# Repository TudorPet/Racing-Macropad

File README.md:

# Racing-Macropad
The Racing Macropad is a compact, programmable input device based on the RP2040 microcontroller, designed for sim racing, gaming, and productivity use cases. It allows full key remapping, encoder customization, and RGB control. The rotary encoder can be used for functions such as brake bias, traction control, menu navigation, or volume control. The device uses Cherry MX–style mechanical switches and connects via USB. Its simple and modular design makes it ideal as a sim racing button box.

---
### Features:
* Compact 3×2 Key Matrix - 6 programmable inputs
* Rotary Encoder - programmable rotary encoder with push button
* 2x RGB LEDs - 2 LEDs for visual feedback
* 3D Printed Case

---
### CAD:
Designed using fusion. Everything fits together using 4x m3 screws and bolts:<br>

---
### Schematic and PCB:
Designed with kicad. I ran DRC and got 0 errors, only a few dismissible warnings. <br>
 <br>

---
### Firmware:
I wrote the firmware using QMK, which was definitely a change compared to what im used to. This was the part of the project that I was looking forward to the least (which may seem weird, as I do enjoy coding), and it turned out to be the most confusing one, too. With that being said, I am looking forward to learning more about QMK and improving.

---

### BOM:
* 1x Seeed XIAO RP2040 at €3.5 - €8.5 (~$4 - $9)
* 6x MX-Style switches at €0.50 - €0.60 (~$0.55 - $0.65) per switch, so €3 - €4 ($3.3 - $4.0) for 6 - if bought in bulk!
* 6x Keycaps at €0.2 (~$0.25) per key, so around €1.2 ($1.45) for 6 - if bought in bulk!
* 1x EC11 Rotary encoder at €4 - €5 (~$4.5 - $5.5)
* 4x M3x16mm screws and 4x M3x5mx4mm heatset inserts at €1 - €3 ($1.1 - $3)
* 1x PCB €5 - €12 ($6 - $13)
* 1x 3D Printed case €5 - €15 ($6 - $17)<br>
These prices are a sheer estimation and, by no means, 100% accurate. Many of these components can be found priced very differently, depending on location and source. The estimated total ranges between €20 and €50 (huge difference, I know!), however I believe it would cost around €30. A big part of the total is the 3d printed case, so the cost is greatly reduced if you own a 3D printer. 
---
### Notes:
This was my first time doing a project like this (and working with programs such as kicad and fusion - which i really enjoyed!). As someone familiar with algorithmics (that also occasionaly helps with repairing/building electronics), I found the design process really fun, however also a bit demanding for a person with so little experience. It took a little bit longer to finish the first version than i would have wanted, however im happy with the way it turned out. I want to keep working on it, implementing features such as syncing the leds to different titles and designing a stand compatible with different racing rigs.

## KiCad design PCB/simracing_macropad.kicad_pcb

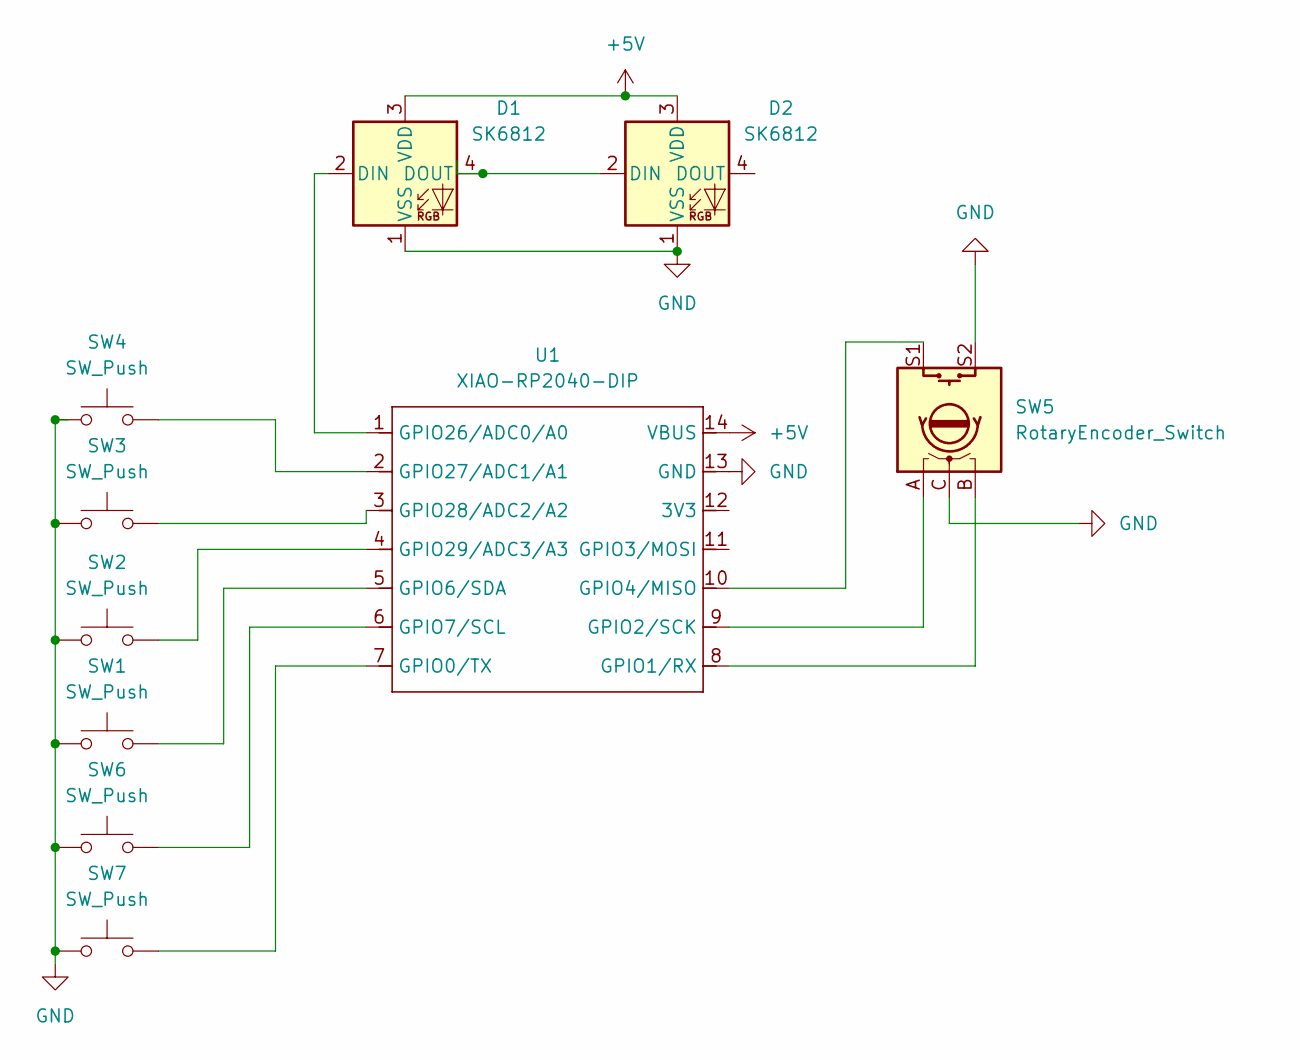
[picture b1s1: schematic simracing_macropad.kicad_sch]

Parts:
D1, D2: SK6812; LED_SK6812_PLCC4_5.0x5.0mm_P3.2mm
SW1, SW2, SW3, SW4, SW6, SW7: SW_Push; SW_Cherry_MX_1.00u_PCB
SW5: RotaryEncoder_Switch; RotaryEncoder_Alps_EC11E-Switch_Vertical_H20mm
U1: XIAO-RP2040-DIP

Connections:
+5V: D1.3 (VDD), D2.3 (VDD), U1.14 (VBUS)
GND: D1.1 (VSS), D2.1 (VSS), SW1.1, SW2.1, SW3.1, SW4.1, SW5.C, SW5.S2, SW6.1, SW7.1, U1.13 (GND)
unnamed: D1.2 (DIN), U1.1 (GPIO26/ADC0/A0)
unnamed: D1.4 (DOUT), D2.2 (DIN)
unnamed: SW7.2, U1.7 (GPIO0/TX)
unnamed: SW5.B, U1.8 (GPIO1/RX)
unnamed: SW5.A, U1.9 (GPIO2/SCK)
unnamed: SW5.S1, U1.10 (GPIO4/MISO)
unnamed: SW1.2, U1.5 (GPIO6/SDA)
unnamed: SW6.2, U1.6 (GPIO7/SCL)
unnamed: SW4.2, U1.2 (GPIO27/ADC1/A1)
unnamed: SW3.2, U1.3 (GPIO28/ADC2/A2)
unnamed: SW2.2, U1.4 (GPIO29/ADC3/A3)

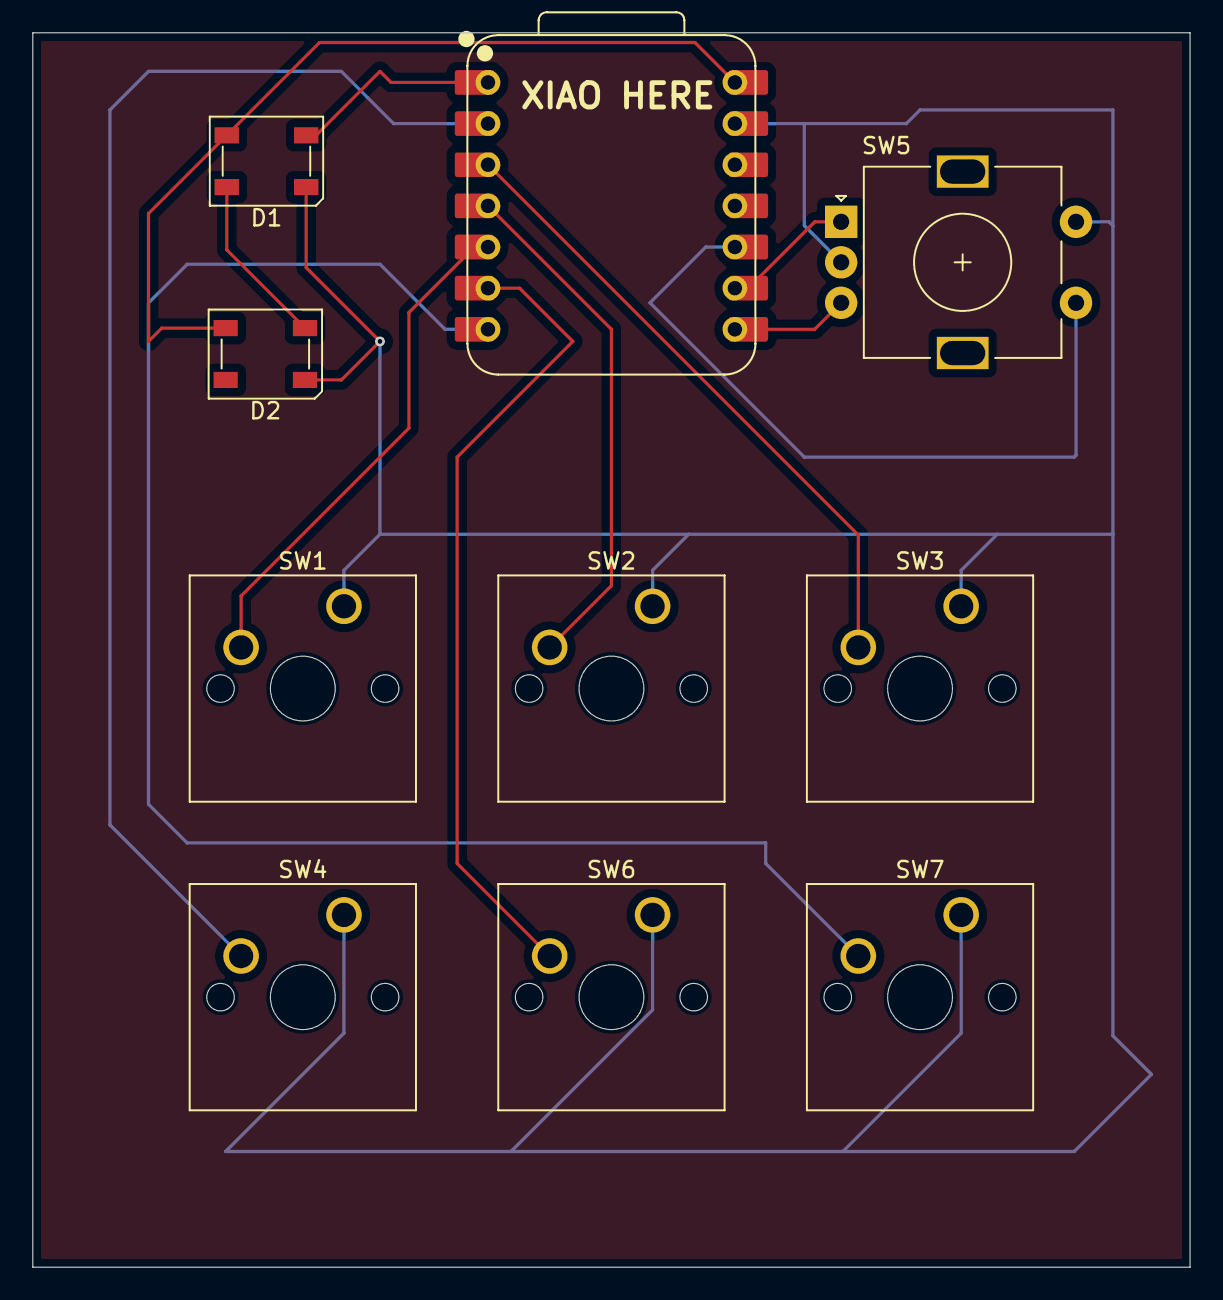
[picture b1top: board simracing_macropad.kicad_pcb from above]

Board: 2 copper layers, 71.4 x 76.2 mm, 10 parts (0 on the bottom side), 13 nets.

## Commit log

2025-12-15 "Kicad basic files for the macropad (the base and top of the case)"
2025-12-15 changed file location
2025-12-15 removed old files
2025-12-16 Uploaded PCB
2025-12-28 Create CAD
2025-12-28 Added Firmware, updated PCB with right files and restructured CAD
2025-12-28 Redesigned case
2025-12-28 Updated code
2025-12-28 Added libraries
2025-12-28 Updated pin numbers
2025-12-28 Updated libraries
